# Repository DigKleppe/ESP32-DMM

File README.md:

# ESP32-DMM
6 digit DMM using ESP32 module
This DMM uses an ESP32 WRoom module as base of the system.
The ADC is a 24 bit ADS1256. The user interface is a 2.8'' TFT and 12 capacitive touchbuttons.
A frontend for voltage, current and Ohms completes the design.
The volts/ohms input is protected for 500V.
The current input has a fuse.

Specifications:
DC/AC true RMS, 10ME input resistance.
Voltage: 250mV - 500V 5 ranges;
Current: 10uA-10A 6 ranges;
Resistance: 1E - 20M, 5 ranges.

The accuracy is targetted at better than 0.1%.
Speed: for hi resolution ( 5-6 digits): 2 readings per second.
For lower resolutions 5 -10 readings per second.

Despite the use of some Aliexpress modules like the ADC ADS1256, it has become a
rather complex design. Not for beginners i suppose.

Remark about the resistors: 0.1% thin film resistors are used. These have better noise preformance.

One of the issues is calibrating, you need a accurate DVM for this.
The calibrating itself is done using a webserver. The calibration data can be up/downloaded
to a host. 

Status of the project 02-21:
Second version. New schematics and PCB, contains corrections of the first prototype. Also better screening to reduce noise.
Not tested yet.
Software: todo: make some changes io-ports.

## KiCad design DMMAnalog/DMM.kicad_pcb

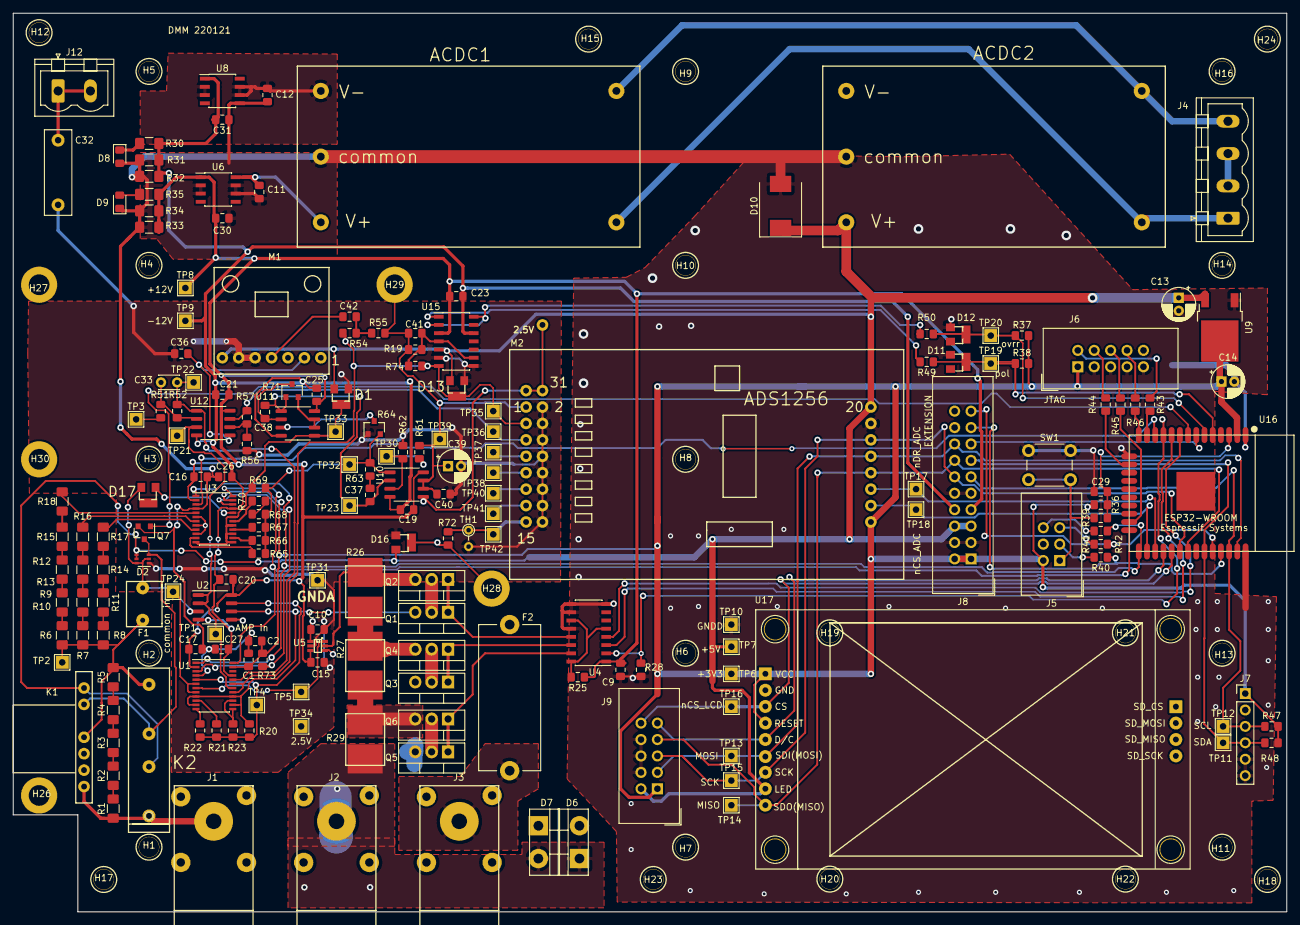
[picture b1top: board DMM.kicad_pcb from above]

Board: 2 copper layers, 197.0 x 139.0 mm, 218 parts (0 on the bottom side), 120 nets.

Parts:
ACDC1: RAC10-15DK; RAC10
ACDC2: RAC10-05SK/277; RAC10
C1, C2, C9, C10, C15, C16, C17, C19, C20, C21, C23, C25, C26, C27, C29, C40, C41, C42: 100n; C_0805_2012Metric_Pad1.15x1.40mm_HandSolder
C11, C12, C30, C31, C36: 1u; C_0805_2012Metric_Pad1.15x1.40mm_HandSolder
C13, C14, C39: 10uV16; CP_Radial_D5.0mm_P2.00mm
C32: 2n2 Y2; C_Rect_L13.0mm_W4.0mm_P10.00mm_FKS3_FKP3_MKS4
C33: 290p; C_Disc_D3.0mm_W2.0mm_P2.50mm
C37: 10n; C_0805_2012Metric_Pad1.15x1.40mm_HandSolder
C38: 330p; C_0805_2012Metric_Pad1.15x1.40mm_HandSolder
D1, D11, D12, D13, D16, D17: BAT754S; SOT-23-handsolder
D2: CMKD6001; SOT-363_SC-70-6
D6, D7: APT30DQ60KG; TO-220-2_Vertical
D8, D9: G; LED_0805_2012Metric_Pad1.15x1.40mm_HandSolder
D10: 1.5SMC6.8A; D_SMC
F1: PTCCL05H100SBE
F2: Fuse; Fuseholder_Cylinder-5x20mm_Stelvio-Kontek_PTF78_Horizontal_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
H1, H2, H3, H4, H5, H6, H7, H8, H9, H10, H11, H12, H13, H14, H15, H16, H17, H18, H19, H20, H21, H22, H23, H24: MountingHole; MountingHole_3.1mm_M3
H26, H27, H28, H29, H30: MountingHole_Pad; MountingHole_3.2mm_M3_DIN965_Pad
J1, J2, J3: Conn_01x01; bananajack-5p
J4: Conn_01x06; PhoenixContact_MSTBVA_2,5_4-G_1x04_P5.00mm_Vertical
J5: bozed header 6p; IDC-Header_2x03_P2.54mm_Vertical
J6, J9: boxed header 2x5; IDC-Header_2x05_P2.54mm_Vertical
J7: Conn_01x06; PinHeader_1x06_P2.54mm_Vertical
J8: Conn_02x10_Odd_Even; IDC-Header_2x10_P2.54mm_Vertical
J12: Conn_01x02; PhoenixContact_MSTBVA_2,5_2-G_1x02_P5.00mm_Vertical
K1: reedrelayboard; reedRelayBoard
K2: Coto 9104-05-10; Relay_SPST_Coto_9104_SIL
M1: LTC1966module; ltc1966module
M2: ADS1256module
Q1, Q2, Q3, Q4, Q5, Q6: IRFB7437PbF; TO-220-3_Vertical
Q7: BSS138; SOT-23
R1, R2, R3, R4, R5, R6, R9, R12, R15, R18: 2M; R_1206_3216Metric_Pad1.42x1.75mm_HandSolder
R7, R10, R13, R16: 105k; R_1206_3216Metric_Pad1.42x1.75mm_HandSolder
R8, R11, R14, R17, R30, R35: 10k; R_1206_3216Metric_Pad1.42x1.75mm_HandSolder
R19, R67, R70: 100k; R_0805_2012Metric_Pad1.15x1.40mm_HandSolder
R20: 200k; R_0805_2012Metric_Pad1.15x1.40mm_HandSolder
R21: 22k; R_0805_2012Metric_Pad1.15x1.40mm_HandSolder
R22, R37, R38, R47, R48, R73: 2k; R_0805_2012Metric_Pad1.15x1.40mm_HandSolder
R23: 200E; R_0805_2012Metric_Pad1.15x1.40mm_HandSolder
R25, R28, R36, R66, R72, R74: 10k; R_0805_2012Metric_Pad1.15x1.40mm_HandSolder
R26: 100mE; 2818kelvin
R27: 10mE; 2818kelvin
R29: 1mE; 2818kelvin
R31, R32, R33, R34: 1k; R_1206_3216Metric_Pad1.42x1.75mm_HandSolder
R39, R40, R41, R42, R63: 100E; R_0805_2012Metric_Pad1.15x1.40mm_HandSolder
R43, R44, R45, R46: 33E; R_0805_2012Metric_Pad1.15x1.40mm_HandSolder
R49, R50, R54, R57, R61, R65: 1k5; R_0805_2012Metric_Pad1.15x1.40mm_HandSolder
R51, R55, R56, R62: 1k; R_0805_2012Metric_Pad1.15x1.40mm_HandSolder
R52: 9k; R_0805_2012Metric_Pad1.15x1.40mm_HandSolder
R64, R71: 100+100k; SOT-23
R68: 1M; R_0805_2012Metric_Pad1.15x1.40mm_HandSolder
R69: 10M; R_0805_2012Metric_Pad1.15x1.40mm_HandSolder
SW1: SW_SPST; SW_PUSH_6mm
TH1: 10k; R_Axial_DIN0204_L3.6mm_D1.6mm_P2.54mm_Vertical
TP1, TP2, TP3, TP4, TP5, TP6, TP7, TP8, TP9, TP10, TP11, TP12, TP13, TP14, TP15, TP16, TP17, TP18, TP19, TP20, TP21, TP22, TP23, TP24, TP30, TP31, TP32, TP33, TP34, TP35, TP36, TP37, TP38, TP39, TP40, TP41, TP42: TestPoint; TestPoint_THTPad_2.0x2.0mm_Drill1.0mm
U1, U3: ADG1414; TSSOP-24_4.4x7.8mm_P0.65mm
U2, U10, U11, U12: OPA2182ID; SO-8_3.9x4.9mm_P1.27mm
U4: TD310; SOIC-16_3.9x9.9mm_P1.27mm
U5: INA213; Texas_R_PDSO-G6
U6: L78L12_SO8; SOIC-8_3.9x4.9mm_P1.27mm
U8: L79L12_SO8; SOIC-8_3.9x4.9mm_P1.27mm
U9: NCP1117-3.3_TO252; TO-252-2
U15: LM339; SOIC-14_3.9x8.7mm_P1.27mm
U16: ESP32-WROOM
U17: 2.2_240x320_sd_spi; 2.2_tft_240x320_sd_spi

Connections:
+1V0: C10.1, C39.1, C40.1, C41.2, D6.1, D7.2, D16.3, H26.1, H27.1, H28.1, H29.1, H30.1, J2.1, M1.3, M2.1, R19.1, R29.2, R51.2, R55.2, R61.2, R72.2, TP3.1, TP34.1, TP39.1, U2.5, U3.6, U3.8, U3.10, U5.1, U5.4, U10.6, U10.7
+3V3: C1.1, C2.1, C14.1, J5.2, J6.1, J7.1, J8.1, J8.2, J9.1, M2.27, R36.2, R37.2, R38.2, R47.2, R48.2, R73.2, TP6.1, U1.23, U3.23, U9.2, U16.2, U17.1, U17.4
+5VD: ACDC2.5, C13.1, D1.2, D2.4, D2.5, D10.1, D13.2, D16.2, J8.5, J8.6, J9.2, K1.1, K2.3, M1.7, M2.20, TP7.1, U9.3, U15.5, U17.8
+12VA: C9.1, C15.1, C16.1, C17.1, C19.1, C20.1, C21.1, C23.1, C25.1, C30.1, J8.7, R25.1, R33.2, R34.2, R35.2, TP8.1, U1.2, U2.8, U3.2, U4.1, U5.3, U6.1, U10.8, U11.8, U12.8, U15.3
-12VA: C19.2, C20.2, C21.2, C23.2, C25.2, C26.1, C27.1, C31.2, J8.8, R30.2, R31.2, R32.2, TP9.1, U1.21, U2.4, U3.21, U8.1, U10.4, U11.4, U12.4, U15.12
/ADC/MISO: J8.14, J9.7, M2.24, TP14.1, U16.31, U17.9
/ADC/MOSI: J8.16, J9.3, M2.23, TP13.1, U16.37, U17.6
/ADC/SCK: J8.12, J9.5, M2.22, TP15.1, U16.30, U17.7
/ADC/channel3: M2.7, TP37.1
/ADC/channel4: M2.9, TP38.1
/ADC/channel5: M2.11, TP40.1
/ADC/channel6: M2.13, TP41.1
/ADC/channel_1: D13.3, M2.3, R54.2, R74.2, TP35.1, U1.17, U1.19, U15.7
/ADC/channel_2: M2.5, R57.1, TP36.1, U12.7
/ADC/nCS_ADC: M2.26, TP18.1, U16.26
/ADC/nDR_ADC: M2.25, TP17.1, U16.27
/ESP32/Curr0_1A: U4.4, U16.9
/ESP32/Curr1A: U4.3, U16.10
/ESP32/Curr10A: R28.1, U4.2, U16.11
/ESP32/DC_LCD: J9.9, U16.28, U17.5
/ESP32/DIN_SHR: U3.3, U16.12
/ESP32/IO35: J8.15, U16.7
/ESP32/RXD0: J8.19, R41.1, U16.34
/ESP32/SCK_SHR: R42.1, U1.1, U3.1, U16.25
/ESP32/SCL: J7.3, J8.11, R47.1, TP12.1, U16.36
/ESP32/SDA: J7.4, J8.13, R48.1, TP11.1, U16.33
/ESP32/TCK: R44.2, U16.16
/ESP32/TDI: R46.2, U16.14
/ESP32/TDO: R45.2, U16.23
/ESP32/TMS: R43.2, U16.13
/ESP32/TXD0: J8.17, R40.1, U16.35
/ESP32/nCS_LCD: J9.10, TP16.1, U16.29, U17.3
/ESP32/nOverrange: D12.3, R37.1, R50.1, TP20.1, U16.6
/ESP32/nPol: D11.3, R38.1, R49.1, TP19.1, U16.5
/ESP32/nReset: C29.1, R36.1, R39.1, U16.3
/ESP32/nSync: U1.24, U3.24, U16.24
/ESP32/relay: Q7.1, U16.8
/VoltInput/commonIn: D2.2, D2.6, D17.2, F1.1, TP24.1, U1.6, U1.8, U2.3
/filter-amplifier/amp-in: TP1.1, TP21.1, U1.18, U2.1, U2.2, U12.3
GNDA: C10.2, C15.2, C32.2, C36.2, C39.2, C40.2, D1.1, D2.1, D13.1, D16.1, M1.5, M1.6, M2.2, M2.4, M2.6, M2.8, M2.10, M2.12, M2.14, M2.16, R56.2, R62.1, R64.1, TH1.2, TP31.1, U5.2, U15.6, U15.8
GNDD: ACDC1.4, ACDC2.4, C1.2, C2.2, C9.2, C11.2, C12.1, C13.2, C14.2, C16.2, C17.2, C26.2, C27.2, C29.2, C30.2, C31.1, D8.2, D9.1, D10.2, D11.1, D12.1, J5.4, J6.3, J6.5, J6.7, J6.9, J7.5, J7.6, J8.3, J8.4, J8.9, J8.10, J9.4, J9.6, J9.8, M2.21, Q7.2, R28.2, R31.1, R32.1, R33.1, R34.1, SW1.1, TP10.1, U1.4, U3.4, U4.8, U4.9, U4.10, U4.12, U6.2, U6.3, U6.6, U6.7, U8.5, U9.1, U16.1, U16.15, U16.38, U17.2
unnamed: ACDC1.1, ACDC2.1, J4.1
unnamed: ACDC1.2, ACDC2.2, J4.4
unnamed: ACDC1.3, C12.2, U8.2, U8.3, U8.6, U8.7
unnamed: ACDC1.5, C11.1, U6.8
unnamed: C32.1, J12.1, J12.2
unnamed: C33.1, R52.1, TP22.1, U1.20, U12.1
unnamed: C33.2, R51.1, R52.2, U12.2
unnamed: C36.1, M1.2, U12.5
unnamed: C37.1, C38.1, R71.1, TP23.1, U10.2, U11.1
unnamed: C37.2, R63.2
unnamed: C38.2, R71.3, U11.2
unnamed: C41.1, R19.2, R74.1, U15.4, U15.9
unnamed: C42.1, R54.1, R55.1
unnamed: C42.2, M1.4
unnamed: D1.3, R69.1, TP33.1, U3.12, U3.13, U3.15, U3.17, U3.19, U11.5
unnamed: D2.3, K1.2, K2.5, Q7.3
unnamed: D6.2, D7.1, F2.1, Q1.3, Q3.3, Q5.3, R20.1, U1.9, U1.11, U1.14, U1.16, U2.6
unnamed: D8.1, R30.1
unnamed: D9.2, R35.1
unnamed: D17.1, U3.20
unnamed: F1.2, K1.4, K2.7, R5.2, R6.2, R7.2, R8.2, TP2.1
unnamed: F2.2, J3.1
unnamed: J1.1, K1.7, K2.1, R1.1
unnamed: J4.2, J4.3
unnamed: J5.1, R39.2, SW1.2
unnamed: J5.3, R40.2
unnamed: J5.5, R41.2
unnamed: J5.6, R42.2
unnamed: J6.2, R43.1
unnamed: J6.4, R44.1
unnamed: J6.6, R45.1
unnamed: J6.8, R46.1
unnamed: M2.15, R72.1, TH1.1, TP42.1
unnamed: M2.30, M2.31, U10.5
unnamed: Q1.1, Q2.1, U4.13
unnamed: Q1.2, Q2.2
unnamed: Q2.3, R26.1, U5.5
unnamed: Q3.1, Q4.1, U4.14
unnamed: Q3.2, Q4.2
unnamed: Q4.3, R26.2, R27.1
unnamed: Q5.1, Q6.1, U4.15
unnamed: Q5.2, Q6.2
unnamed: Q6.3, R27.2, R29.1
unnamed: R1.2, R2.1
unnamed: R2.2, R3.1
unnamed: R3.2, R4.1
unnamed: R4.2, R5.1
unnamed: R6.1, R9.2
unnamed: R10.1, R13.2
unnamed: R7.1, R10.2
unnamed: R11.1, R14.2
unnamed: R8.1, R11.2
unnamed: R12.1, R15.2
unnamed: R9.1, R12.2
unnamed: R13.1, R16.2
unnamed: R14.1, R17.2
unnamed: R15.1, R18.2
unnamed: R16.1, U3.7
unnamed: R17.1, U3.9
unnamed: R18.1, U3.5
unnamed: R20.2, R21.2, R22.2, R23.2, TP4.1, U1.5, U2.7
unnamed: R21.1, U1.10
unnamed: R22.1, U1.12
unnamed: R23.1, U1.13, U1.15
unnamed: R25.2, U4.5, U4.11, U4.16
unnamed: R49.2, U15.1
unnamed: R50.2, U15.2, U15.14
unnamed: R56.1, R57.2, U12.6
unnamed: R61.1, R62.2, TP30.1, U10.3
unnamed: R63.1, R64.2, R65.2, R66.2, R67.2, R68.2, R69.2, TP32.1, U10.1
unnamed: R64.3, U11.3
unnamed: R65.1, U3.11
unnamed: R66.1, U3.14
unnamed: R67.1, U3.16
unnamed: R68.1, R70.2
unnamed: R70.1, U3.18
unnamed: R71.2, U11.6, U11.7
unnamed: R73.1, U1.3, U3.22
unnamed: TP5.1, U1.7, U5.6

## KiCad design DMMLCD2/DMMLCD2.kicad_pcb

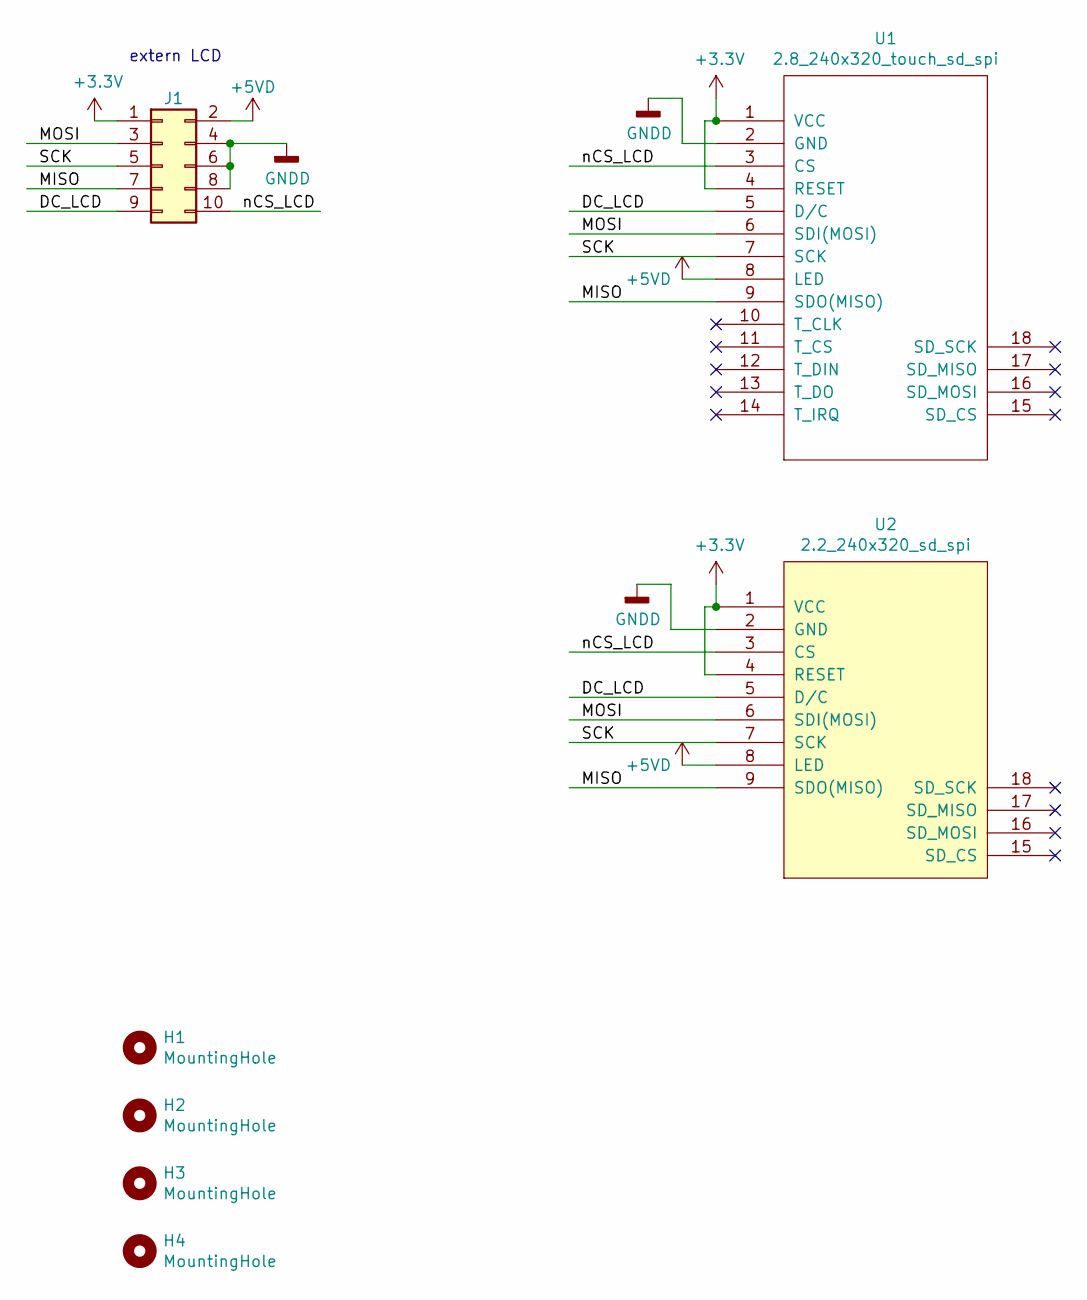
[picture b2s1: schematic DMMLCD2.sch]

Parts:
H1, H2, H3, H4: MountingHole; MountingHole_3.2mm_M3
J1: boxed header 2x5; IDC-Header_2x05_P2.54mm_Vertical
U1: 2.8_240x320_touch_sd_spi; 2.8_tft_240x320_touch_sd_spi
U2: 2.2_240x320_sd_spi; 2.2_tft_240x320_sd_spi

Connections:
+3V3: J1.1, U1.1 (VCC), U1.4 (RESET), U2.1 (VCC), U2.4 (RESET)
+5VD: J1.2, U1.8 (LED), U2.8 (LED)
/DC_LCD: J1.9, U1.5 (D/C), U2.5 (D/C)
/MISO: J1.7, U1.9 (SDO(MISO)), U2.9 (SDO(MISO))
/MOSI: J1.3, U1.6 (SDI(MOSI)), U2.6 (SDI(MOSI))
/SCK: J1.5, U1.7 (SCK), U2.7 (SCK)
/nCS_LCD: J1.10, U1.3 (CS), U2.3 (CS)
GNDD: J1.4, J1.6, J1.8, U1.2 (GND), U2.2 (GND)

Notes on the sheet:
extern LCD

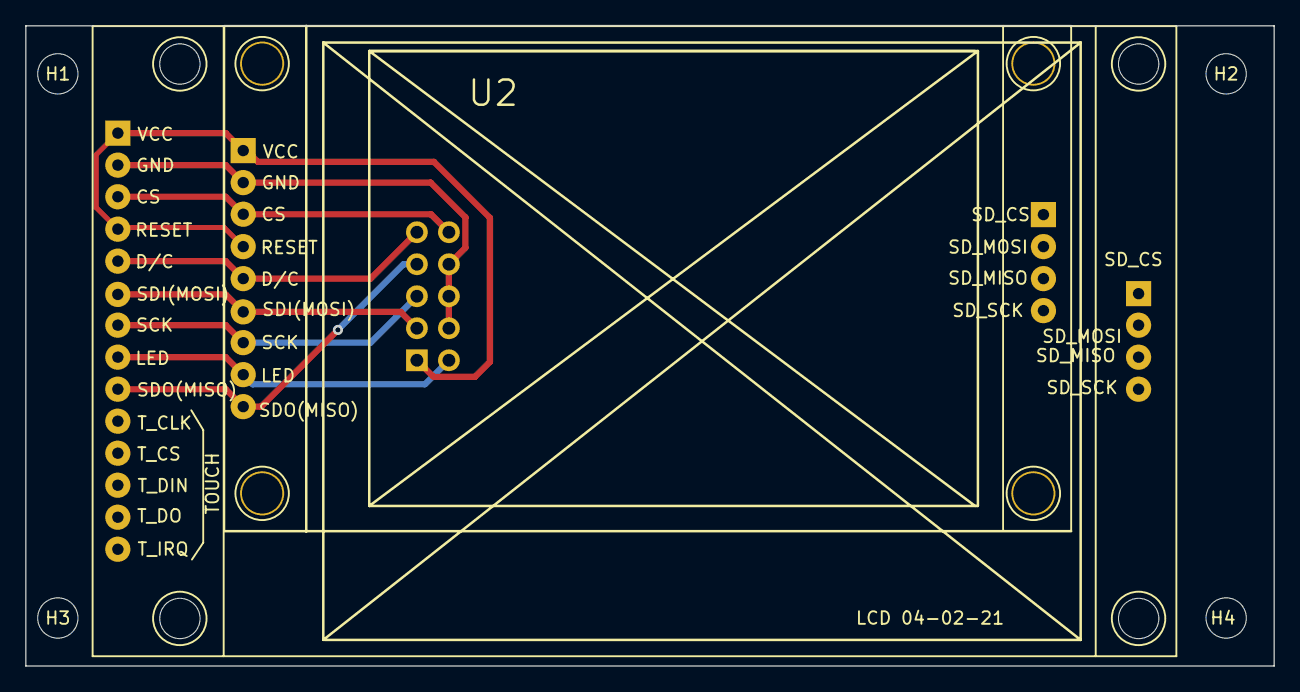
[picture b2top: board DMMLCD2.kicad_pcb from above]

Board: 2 copper layers, 99.1 x 50.8 mm, 7 parts (1 on the bottom side), 8 nets.

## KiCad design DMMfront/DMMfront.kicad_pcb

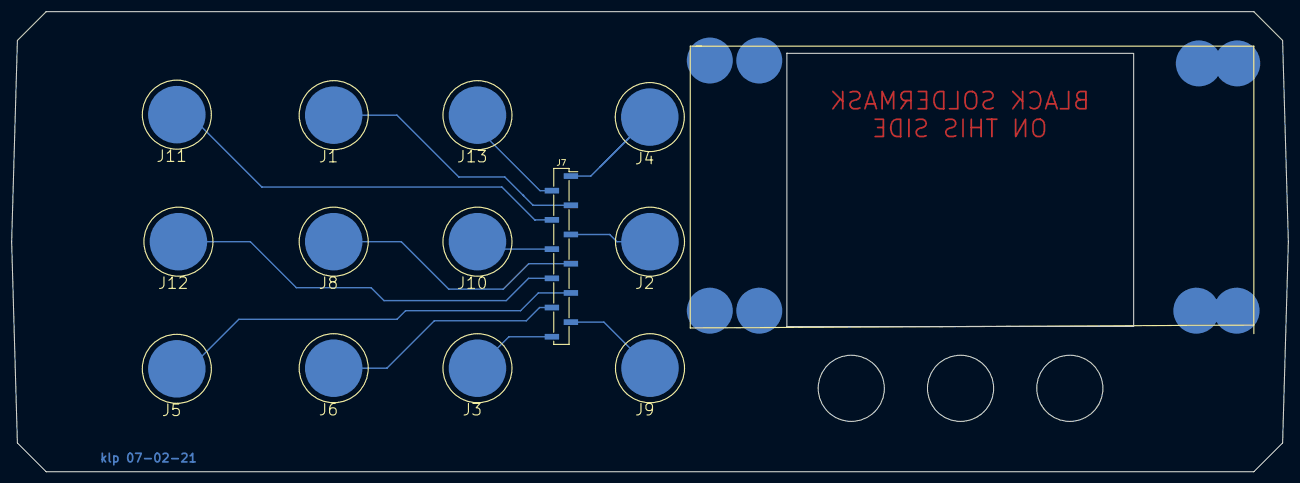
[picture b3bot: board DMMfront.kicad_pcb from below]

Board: 2 copper layers, 222.0 x 80.0 mm, 17 parts (13 on the bottom side), 12 nets.

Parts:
H5, H6, H7: Jack hole; hole11.5
J1, J2, J3, J4, J5, J6, J8, J9, J10, J11, J12, J13: Conn_01x01; touchpad10
J7: Conn_01x12; PinHeader_1x12_P2.54mm_Vertical_SMD_Pin1Right
lcd1: lcdfront; 2.8_tft_front

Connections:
unnamed: J1.1, J7.3
unnamed: J2.1, J7.5
unnamed: J3.1, J7.12
unnamed: J4.1, J7.1
unnamed: J5.1, J7.9
unnamed: J6.1, J7.10
unnamed: J7.7, J8.1
unnamed: J7.11, J9.1
unnamed: J7.6, J10.1
unnamed: J7.4, J11.1
unnamed: J7.8, J12.1
unnamed: J7.2, J13.1

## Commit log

2021-02-07 doc updated
